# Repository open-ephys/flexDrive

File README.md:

flexDrive
==========

__This design is deprecated, we recommend switching to the newer Open Ephys shuttle drive__ (preprint: https://www.biorxiv.org/content/10.1101/746651v1), (git repository: https://github.com/open-ephys/shuttle-drive). This new design is superior to the flexDrive in all aspects (robustness, travel distance, build speed), and we strongly recommend switching.

The flexDrive is a compact hyperdrive for up to 16 independently movable electrodes. It uses a novel spring mechanism to adjust electrode depth.

This repository only contains design files. See https://open-ephys.atlassian.net/wiki/display/OEW/flexDrive for documentation and assembly instructions.

File types
------------
- .brd = EAGLE board files; describe the physical layout of the printed circuit board
- .md = Markdown files; most likely a README file; can be viewed with any text edtior
- .txt  = standard text files
- "gerber" files (.top, .bsk, .oln, etc.) = contain machine-readable instructions for creating the printed circuit board; these are sent to a fab house (such as Sunstone Circuits) for PCB production
- .SLDPRT files = SolidWorks part files; contain CAD models of 3D components
- .SLDDRW files = SolidWorks drawing files; contain 2D images of components
- .DXF = another type of 2D drawing file that can be opened in Adobe Illustrator or similar software
- .STL files = stereolithography files; can be sent to a rapid prototyping service (such as Shapeways) to create 3D objects
- .pdf files = standard document format for viewing and editing 2D images

Paper
----------

Voigts J, Siegle JH, Pritchett DL and Moore CI (2013). 
The flexDrive: An ultra-light implant for optical control and highly parallel chronic recording of neuronal ensembles in freely moving mice. 
Front. Syst. Neurosci. 7:8. doi: 10.3389/fnsys.2013.00008

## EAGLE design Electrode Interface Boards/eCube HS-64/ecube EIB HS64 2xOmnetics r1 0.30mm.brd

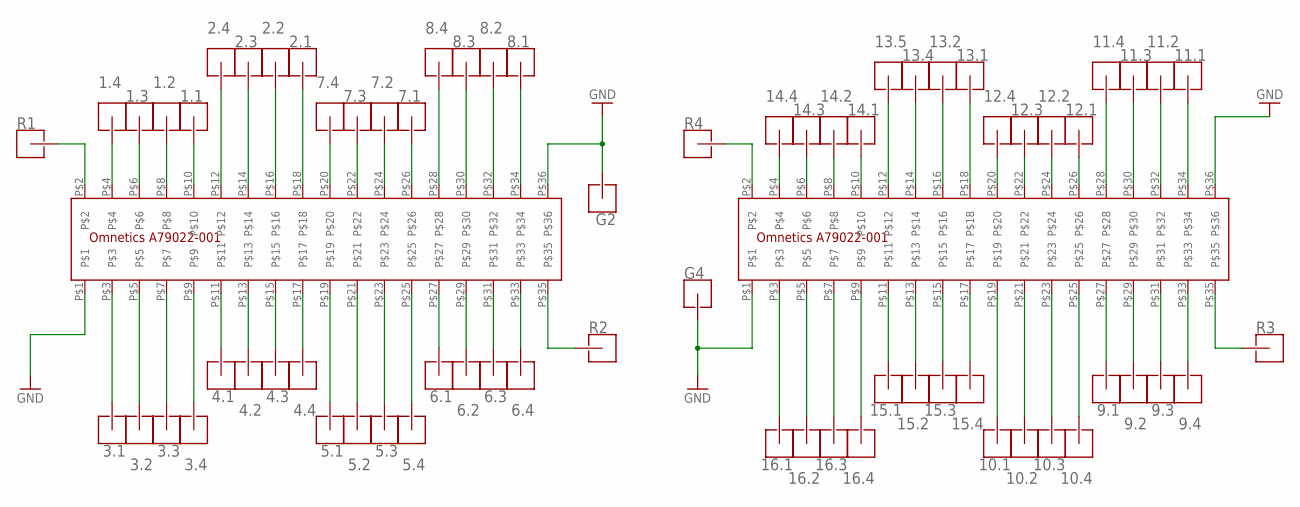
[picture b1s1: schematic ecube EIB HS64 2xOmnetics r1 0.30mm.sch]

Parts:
1.1, 1.2, 1.3, 1.4, 2.1, 2.2, 2.3, 2.4, 3.1, 3.2, 3.3, 3.4, 4.1, 4.2, 4.3, 4.4, 5.1, 5.2, 5.3, 5.4, 6.1, 6.2, 6.3, 6.4, 7.1, 7.2, 7.3, 7.4, 8.1, 8.2, 8.3, 8.4, 9.1, 9.2, 9.3, 9.4, 10.1, 10.2, 10.3, 10.4, 11.1, 11.2, 11.3, 11.4, 12.1, 12.2, 12.3, 12.4, 13.1, 13.2, 13.4, 13.5, 14.1, 14.2, 14.3, 14.4, 15.1, 15.2, 15.3, 15.4, 16.1, 16.2, 16.3, 16.4: HOLE_S_G_PIN_V3; SMALL_GOLD_PIN_V3
G2, G4: HOLE_L_G_PIN_V1; LARGE_GOLD_PIN_V1
R1, R2, R3, R4: HOLE_L_G_PIN_V1; LARGE_GOLD_PIN_V1
U$1, U$2: A79022-001

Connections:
GND: G2.P$1, G4.P$1, U$1.P$1, U$1.P$36, U$2.P$1, U$2.P$36
unnamed: R4.P$1, U$2.P$2
unnamed: R2.P$1, U$1.P$35
unnamed: R1.P$1, U$1.P$2
unnamed: 14.4.P$1, U$2.P$4
unnamed: 14.3.P$1, U$2.P$6
unnamed: 14.2.P$1, U$2.P$8
unnamed: 14.1.P$1, U$2.P$10
unnamed: 13.5.P$1, U$2.P$12
unnamed: 13.4.P$1, U$2.P$14
unnamed: 13.2.P$1, U$2.P$16
unnamed: 13.1.P$1, U$2.P$18
unnamed: 12.4.P$1, U$2.P$20
unnamed: 12.3.P$1, U$2.P$22
unnamed: 12.2.P$1, U$2.P$24
unnamed: 12.1.P$1, U$2.P$26
unnamed: 11.4.P$1, U$2.P$28
unnamed: 11.3.P$1, U$2.P$30
unnamed: 11.2.P$1, U$2.P$32
unnamed: 11.1.P$1, U$2.P$34
unnamed: 9.4.P$1, U$2.P$33
unnamed: 9.3.P$1, U$2.P$31
unnamed: R3.P$1, U$2.P$35
unnamed: 9.2.P$1, U$2.P$29
unnamed: 9.1.P$1, U$2.P$27
unnamed: 10.4.P$1, U$2.P$25
unnamed: 10.3.P$1, U$2.P$23
unnamed: 10.2.P$1, U$2.P$21
unnamed: 10.1.P$1, U$2.P$19
unnamed: 15.4.P$1, U$2.P$17
unnamed: 15.3.P$1, U$2.P$15
unnamed: 15.2.P$1, U$2.P$13
unnamed: 15.1.P$1, U$2.P$11
unnamed: 3.1.P$1, U$1.P$3
unnamed: 16.4.P$1, U$2.P$9
unnamed: 16.3.P$1, U$2.P$7
unnamed: 3.2.P$1, U$1.P$5
unnamed: 3.3.P$1, U$1.P$7
unnamed: 3.4.P$1, U$1.P$9
unnamed: 4.1.P$1, U$1.P$11
unnamed: 4.2.P$1, U$1.P$13
unnamed: 4.3.P$1, U$1.P$15
unnamed: 4.4.P$1, U$1.P$17
unnamed: 5.1.P$1, U$1.P$19
unnamed: 5.2.P$1, U$1.P$21
unnamed: 5.3.P$1, U$1.P$23
unnamed: 5.4.P$1, U$1.P$25
unnamed: 6.1.P$1, U$1.P$27
unnamed: 6.2.P$1, U$1.P$29
unnamed: 6.3.P$1, U$1.P$31
unnamed: 6.4.P$1, U$1.P$33
unnamed: 16.2.P$1, U$2.P$5
unnamed: 16.1.P$1, U$2.P$3
unnamed: 8.1.P$1, U$1.P$34
unnamed: 8.2.P$1, U$1.P$32
unnamed: 8.3.P$1, U$1.P$30
unnamed: 8.4.P$1, U$1.P$28
unnamed: 7.1.P$1, U$1.P$26
unnamed: 7.2.P$1, U$1.P$24
unnamed: 7.3.P$1, U$1.P$22
unnamed: 7.4.P$1, U$1.P$20
unnamed: 2.1.P$1, U$1.P$18
unnamed: 2.2.P$1, U$1.P$16
unnamed: 2.3.P$1, U$1.P$14
unnamed: 2.4.P$1, U$1.P$12
unnamed: 1.1.P$1, U$1.P$10
unnamed: 1.2.P$1, U$1.P$8
unnamed: 1.3.P$1, U$1.P$6
unnamed: 1.4.P$1, U$1.P$4

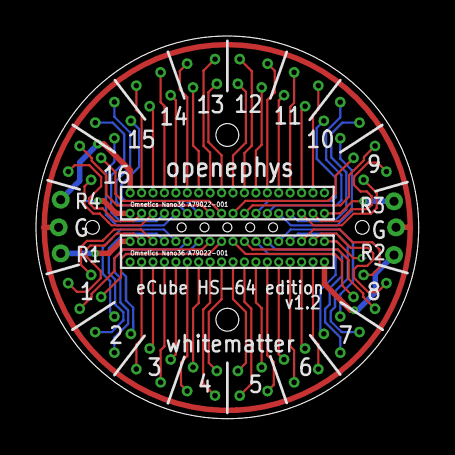
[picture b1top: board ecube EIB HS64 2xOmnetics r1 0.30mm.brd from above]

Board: 2 copper layers, 21.3 x 21.3 mm, 72 parts (0 on the bottom side), 69 nets.

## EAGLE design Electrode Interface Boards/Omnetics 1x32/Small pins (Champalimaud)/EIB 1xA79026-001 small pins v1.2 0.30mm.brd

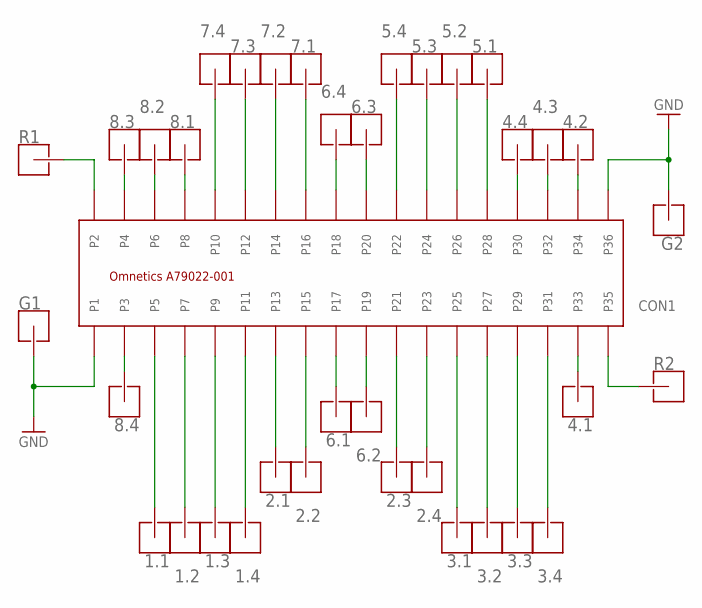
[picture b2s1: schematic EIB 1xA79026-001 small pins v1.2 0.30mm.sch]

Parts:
1.1, 1.2, 1.3, 1.4, 2.1, 2.2, 2.3, 2.4, 3.1, 3.2, 3.3, 3.4, 4.1, 4.2, 4.3, 4.4, 5.1, 5.2, 5.3, 5.4, 6.1, 6.2, 6.3, 6.4, 7.1, 7.2, 7.3, 7.4, 8.1, 8.2, 8.3, 8.4: HOLE_S_G_PIN_V3; SMALL_GOLD_PIN_V3
CON1: A79022-001_MALESMD; A79026-001_MALE
G1, G2: HOLE_S_G_PIN_V3; SMALL_GOLD_PIN_V3
R1, R2: HOLE_S_G_PIN_V3; SMALL_GOLD_PIN_V3

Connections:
GND: CON1.P1, CON1.P36, G1.P$1, G2.P$1
unnamed: 1.1.P$1, CON1.P5
unnamed: 1.2.P$1, CON1.P7
unnamed: 1.3.P$1, CON1.P9
unnamed: 4.1.P$1, CON1.P33
unnamed: 4.3.P$1, CON1.P32
unnamed: 4.2.P$1, CON1.P34
unnamed: 1.4.P$1, CON1.P11
unnamed: 4.4.P$1, CON1.P30
unnamed: 6.1.P$1, CON1.P17
unnamed: 6.2.P$1, CON1.P19
unnamed: 6.3.P$1, CON1.P20
unnamed: 7.3.P$1, CON1.P12
unnamed: 2.1.P$1, CON1.P13
unnamed: 2.2.P$1, CON1.P15
unnamed: 2.3.P$1, CON1.P21
unnamed: 2.4.P$1, CON1.P23
unnamed: 3.1.P$1, CON1.P25
unnamed: 3.2.P$1, CON1.P27
unnamed: 3.3.P$1, CON1.P29
unnamed: 3.4.P$1, CON1.P31
unnamed: 6.4.P$1, CON1.P18
unnamed: 8.4.P$1, CON1.P3
unnamed: 8.3.P$1, CON1.P4
unnamed: 8.2.P$1, CON1.P6
unnamed: 8.1.P$1, CON1.P8
unnamed: 7.2.P$1, CON1.P14
unnamed: 7.1.P$1, CON1.P16
unnamed: 7.4.P$1, CON1.P10
unnamed: 5.1.P$1, CON1.P28
unnamed: 5.2.P$1, CON1.P26
unnamed: 5.4.P$1, CON1.P22
unnamed: 5.3.P$1, CON1.P24
unnamed: CON1.P2, R1.P$1
unnamed: CON1.P35, R2.P$1

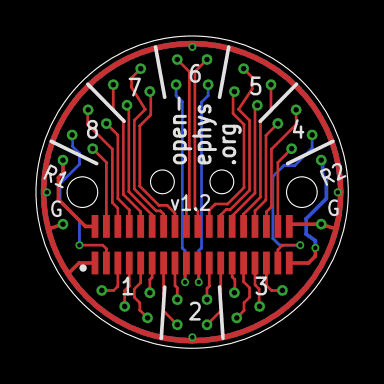
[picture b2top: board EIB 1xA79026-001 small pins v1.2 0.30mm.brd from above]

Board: 2 copper layers, 17.3 x 17.3 mm, 37 parts (0 on the bottom side), 35 nets.

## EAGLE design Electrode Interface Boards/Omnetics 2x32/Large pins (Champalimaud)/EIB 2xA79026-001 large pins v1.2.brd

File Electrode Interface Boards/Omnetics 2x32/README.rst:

2x Omnetics 36-channel "nano-strip" connectors, 4 guide posts
---------------------------------------------------------------------------------

The 64ch_eib_omnetics_3fibers Electrode Interface Board  (EIB) is designed to form a connection between 64 microwire electrodes or individual wires forming stereotrodes or tetrodes, and two 32 channel omnetics connectors.

The 'offset variant' provides more space between the two omnetics connectors and can be soldered by hand if needed, but won't fit the 64 channel headstage.

The aligned variant fits the 64 channel headstage, and can also be used with 2x 32 channel headstages, if they're aligned with the PCB facing away from the center (this will affect the channel mapping).

See the documentation on https://open-ephys.atlassian.net/wiki/display/OEW/flexDrive for building and use instructions.

**WARNING:** These designs will not work if fabricated as 'standard quality' PCB, see Fabrication instructions and get in touch with your PCB maker before placing orders!

Connectors on EIB:
~~~~~~~~~~~~~~~

* male surface-mount vertical (A79026-001 / NPD-36-VV-GS)

Connectors on Headstage:
~~~~~~~~~~~~~~~~~~
 
* female surface-mount horizontal (A79025-001 / NSD-36-AA-GS)
* female surface-mount vertical (A79027-001 / NSD-36-VV-GS)

Pin mapping:
~~~~~~~~~~~~~~~~~~
The pin mapping for the GROUND and REFERENCE channels on the offset connector EIB are compatible with the mapping on the Intan evaluation system headstages (http://www.intantech.com/files/Intan_RHD2000_eval_system.pdf) and the open-ephys headstages (open-ephys.org)

(viewed down onto the eib, looking onto the bottom of the headstage connector this would be flipped)

| ref  | ch | ch | ... | ch | gnd |
| gnd | ch | ch | ... | ch | ref |

For channel mappings of individual EIB designs, look at the documenttaiopn in that EIBs folder. Orientation of headstages affects the channel mapping - when in doubt you should sanity check your mapping by connecting a EIB to your system and grounding out or injecting a signal on individual vias.

Hole sizes:
~~~~~~~~~~~~~~~~~~

The hole size on this EIB (0.3mm) is suited for use with SMALL neuralynx gold pins (http://neuralynx.com/products/electrode_interface_boards/eib_pins) 

The three mounting holes for optical fiber ferrules are sized for use with 1.25mm OD ferrules.

See the documentation on https://open-ephys.atlassian.net/wiki/display/OEW/flexDrive for building and use instructions.

Fabrication instructions:
~~~~~~~~~~~~~~~~~~

These EIBs can be fabricated with the following process
- 5mil trace with / 5mil trace space
- gold immersion finish
- 0.03 inch board thickness (not critical, can be made thicker)
- top silkscreen

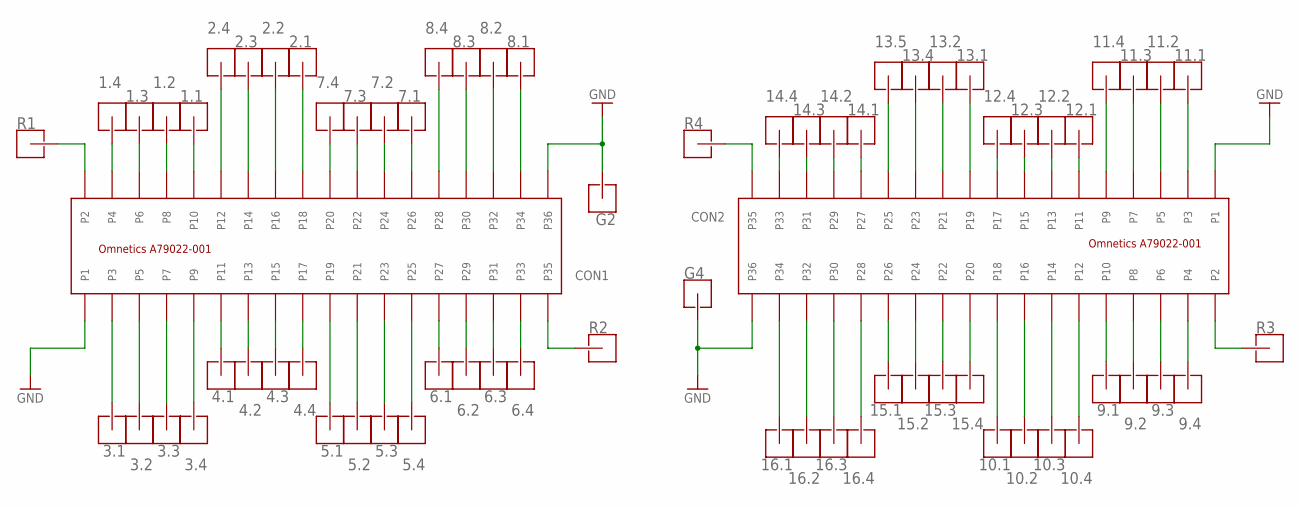
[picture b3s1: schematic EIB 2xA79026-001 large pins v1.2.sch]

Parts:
1.1, 1.2, 1.3, 1.4, 2.1, 2.2, 2.3, 2.4, 3.1, 3.2, 3.3, 3.4, 4.1, 4.2, 4.3, 4.4, 5.1, 5.2, 5.3, 5.4, 6.1, 6.2, 6.3, 6.4, 7.1, 7.2, 7.3, 7.4, 8.1, 8.2, 8.3, 8.4, 9.1, 9.2, 9.3, 9.4, 10.1, 10.2, 10.3, 10.4, 11.1, 11.2, 11.3, 11.4, 12.1, 12.2, 12.3, 12.4, 13.1, 13.2, 13.4, 13.5, 14.1, 14.2, 14.3, 14.4, 15.1, 15.2, 15.3, 15.4, 16.1, 16.2, 16.3, 16.4: HOLE_L_G_PIN_V5; LARGE_GOLD_PIN_V5
CON1, CON2: A79022-001_MALESMD; A79026-001_MALE
G2, G4: HOLE_L_G_PIN_V5; LARGE_GOLD_PIN_V5
R1, R2, R3, R4: HOLE_L_G_PIN_V5; LARGE_GOLD_PIN_V5

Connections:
GND: CON1.P1, CON1.P36, CON2.P1, CON2.P36, G2.P$1, G4.P$1
unnamed: 11.2.P$1, CON2.P5
unnamed: 11.3.P$1, CON2.P7
unnamed: 11.4.P$1, CON2.P9
unnamed: 14.4.P$1, CON2.P33
unnamed: 16.2.P$1, CON2.P32
unnamed: 16.1.P$1, CON2.P34
unnamed: 12.1.P$1, CON2.P11
unnamed: 16.3.P$1, CON2.P30
unnamed: 12.4.P$1, CON2.P17
unnamed: 13.1.P$1, CON2.P19
unnamed: 15.4.P$1, CON2.P20
unnamed: 10.4.P$1, CON2.P12
unnamed: 12.2.P$1, CON2.P13
unnamed: 12.3.P$1, CON2.P15
unnamed: 13.2.P$1, CON2.P21
unnamed: 13.4.P$1, CON2.P23
unnamed: 13.5.P$1, CON2.P25
unnamed: 14.1.P$1, CON2.P27
unnamed: 14.2.P$1, CON2.P29
unnamed: 14.3.P$1, CON2.P31
unnamed: 10.1.P$1, CON2.P18
unnamed: 11.1.P$1, CON2.P3
unnamed: 9.4.P$1, CON2.P4
unnamed: 9.3.P$1, CON2.P6
unnamed: 9.2.P$1, CON2.P8
unnamed: 10.3.P$1, CON2.P14
unnamed: 10.2.P$1, CON2.P16
unnamed: 9.1.P$1, CON2.P10
unnamed: 16.4.P$1, CON2.P28
unnamed: 15.1.P$1, CON2.P26
unnamed: 15.3.P$1, CON2.P22
unnamed: 15.2.P$1, CON2.P24
unnamed: CON1.P2, R1.P$1
unnamed: CON2.P2, R3.P$1
unnamed: CON2.P35, R4.P$1
unnamed: CON1.P35, R2.P$1
unnamed: 3.2.P$1, CON1.P5
unnamed: 3.3.P$1, CON1.P7
unnamed: 3.4.P$1, CON1.P9
unnamed: 4.1.P$1, CON1.P11
unnamed: 4.2.P$1, CON1.P13
unnamed: 4.3.P$1, CON1.P15
unnamed: 5.2.P$1, CON1.P21
unnamed: 5.3.P$1, CON1.P23
unnamed: 5.4.P$1, CON1.P25
unnamed: 7.4.P$1, CON1.P20
unnamed: 7.3.P$1, CON1.P22
unnamed: 7.2.P$1, CON1.P24
unnamed: 4.4.P$1, CON1.P17
unnamed: 5.1.P$1, CON1.P19
unnamed: 7.1.P$1, CON1.P26
unnamed: 2.1.P$1, CON1.P18
unnamed: 3.1.P$1, CON1.P3
unnamed: 1.4.P$1, CON1.P4
unnamed: 1.3.P$1, CON1.P6
unnamed: 1.2.P$1, CON1.P8
unnamed: 2.4.P$1, CON1.P12
unnamed: 2.3.P$1, CON1.P14
unnamed: 2.2.P$1, CON1.P16
unnamed: 1.1.P$1, CON1.P10
unnamed: 6.4.P$1, CON1.P33
unnamed: 6.1.P$1, CON1.P27
unnamed: 6.2.P$1, CON1.P29
unnamed: 6.3.P$1, CON1.P31
unnamed: 8.1.P$1, CON1.P34
unnamed: 8.2.P$1, CON1.P32
unnamed: 8.3.P$1, CON1.P30
unnamed: 8.4.P$1, CON1.P28

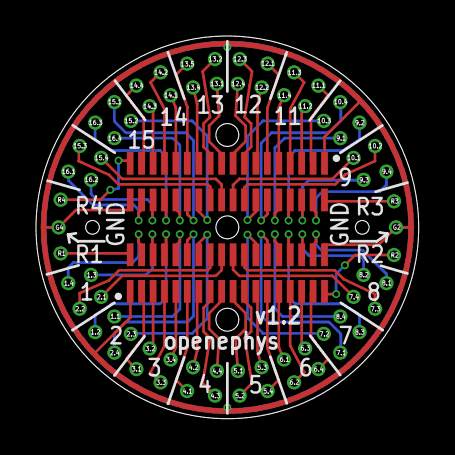
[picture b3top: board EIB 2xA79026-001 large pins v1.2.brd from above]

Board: 2 copper layers, 21.3 x 21.3 mm, 72 parts (0 on the bottom side), 69 nets.

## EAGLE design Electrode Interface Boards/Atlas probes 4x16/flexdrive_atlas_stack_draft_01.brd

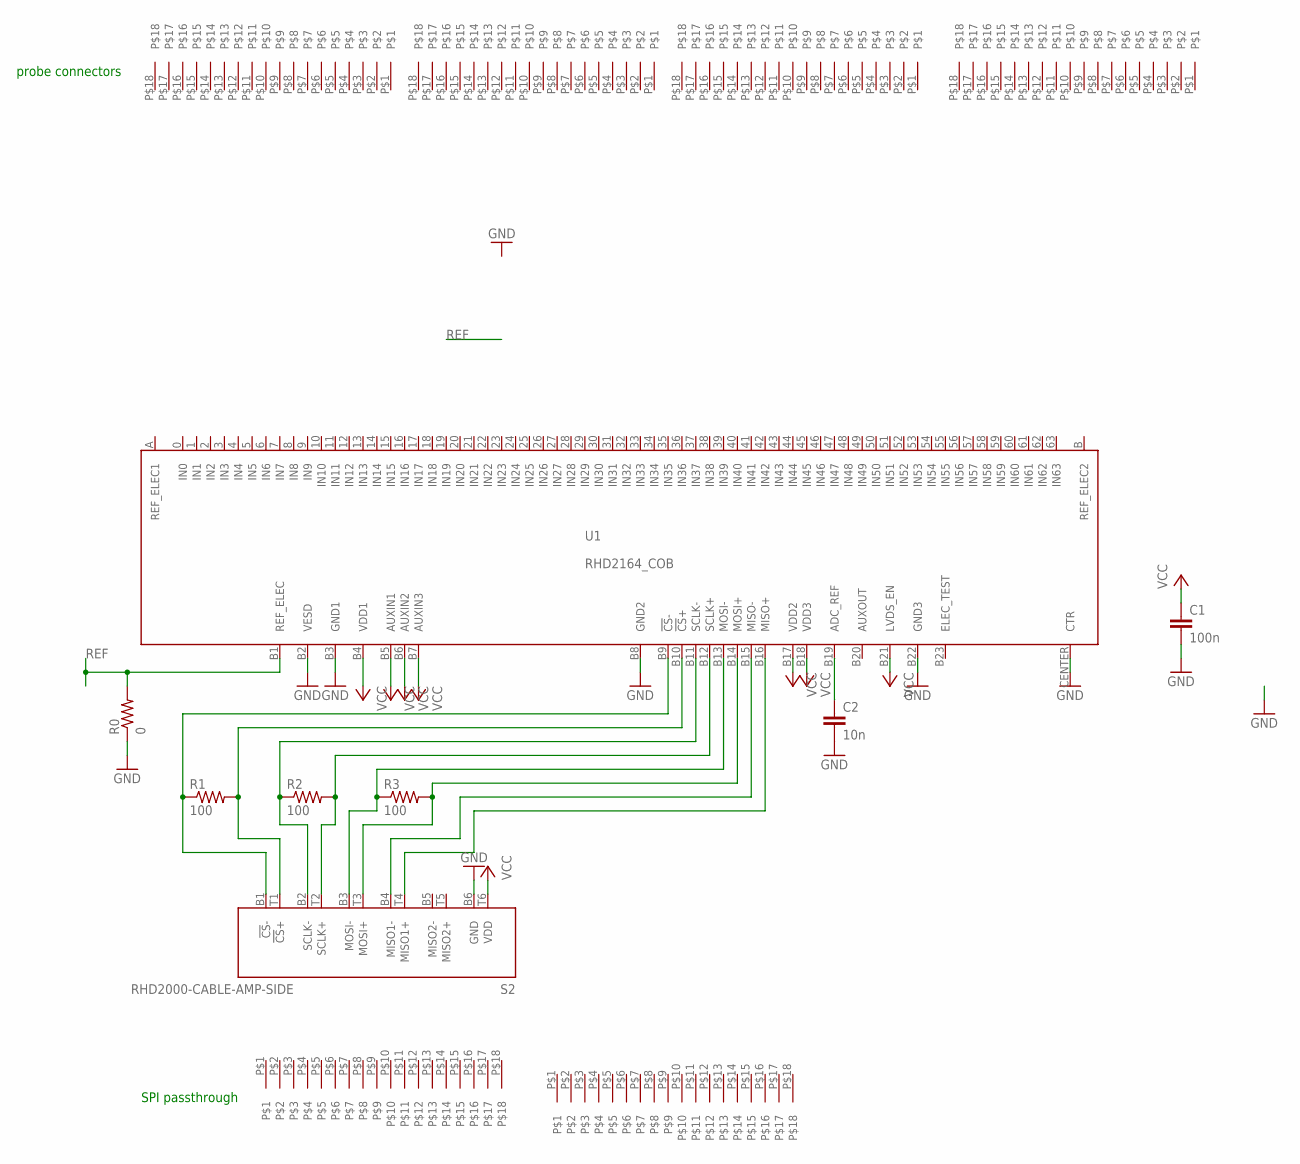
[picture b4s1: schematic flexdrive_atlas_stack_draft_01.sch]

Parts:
C1: 100n; 0402
C2: 10n; 0201
R0: 0; 0402
R1, R2, R3: 100; 0201
S2: RHD2000-CABLE-AMP-SIDE; OMNETICS_PZN-12-AA
U1: RHD2164_COB
U$1, U$2, U$3, U$4, U$5, U$6: 18PIN_035MM_SLIMSTACK; 18PIN_025MM_SLIMSTACK

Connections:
GND: C1.2, C2.2, R0.1, S2.B6 (GND), U1.B2 (VESD), U1.B3 (GND1), U1.B8 (GND2), U1.B22 (GND3), U1.CENTER (CTR)
unnamed: S2.T4 (MISO1+), U1.B16 (MISO+)
unnamed: R1.1, S2.B1 (!CS!-), U1.B9 (!CS!-)
unnamed: R1.2, S2.T1 (!CS!+), U1.B10 (!CS!+)
unnamed: R2.1, S2.B2 (SCLK-), U1.B11 (SCLK-)
unnamed: R2.2, S2.T2 (SCLK+), U1.B12 (SCLK+)
unnamed: R3.1, S2.B3 (MOSI-), U1.B13 (MOSI-)
unnamed: R3.2, S2.T3 (MOSI+), U1.B14 (MOSI+)
unnamed: S2.B4 (MISO1-), U1.B15 (MISO-)
unnamed: C2.1, U1.B19 (ADC_REF)
REF: R0.2, U1.B1 (REF_ELEC)
VCC: C1.1, S2.T6 (VDD), U1.B4 (VDD1), U1.B5 (AUXIN1), U1.B6 (AUXIN2), U1.B7 (AUXIN3), U1.B17 (VDD2), U1.B18 (VDD3), U1.B21 (LVDS_EN)

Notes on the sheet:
SPI passthrough
probe connectors

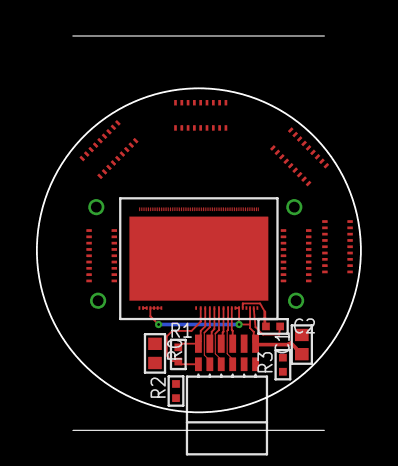
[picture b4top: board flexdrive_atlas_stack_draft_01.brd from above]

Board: 2 copper layers, 18.0 x 18.0 mm, 14 parts (0 on the bottom side), 12 nets.

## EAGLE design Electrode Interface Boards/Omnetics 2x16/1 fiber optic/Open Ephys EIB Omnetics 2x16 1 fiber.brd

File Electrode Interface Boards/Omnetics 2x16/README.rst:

Omnetics 18-channel "nano-strip" connectors, 4 guide posts
---------------------------------------------------------------------------------

The 32ch_eib_omnetics_2fibers and 32ch_eib_omnetics_1fiber Electrode Interface Boards (EIB) aredesigned to form a connection between 32microwire electrodes or individual wires forming stereotrodes or tetrodes, and two 16 channel omnetics connectors.

See the documentation on http://github.com/open-ephys/flexDrive for building and use instructions.

Connectors on EIB:
~~~~~~~~~~~~~~~

* male surface-mount vertical (A79042-001 / NPD-18-VV-GS)

Connectors on Headstage:
~~~~~~~~~~~~~~~~~~
 
* female surface mount horizontal (A79041-001 / NSD-18-AA-GS)
* female surface mount vertical (A79043-001 / NSD-18-VV-GS)

Pin mapping:
~~~~~~~~~~~~~~~~~~
The pin mapping for the GROUND and REFERENCE channels on this EIB are compatible with the mapping on the standard omnetics 16 channel headstages.

Hole sizes:
~~~~~~~~~~~~~~~~~~
The hole size on this EIB (0.5mm) is suited for use with LARGE neuralynx gold pins (http://neuralynx.com/products/electrode_interface_boards/eib_pins) 

The mounting holes for optical fiber ferrules are sized for use with 1.25mm OD ferrules.

Fabrication instructions:
~~~~~~~~~~~~~~~~~~

This EIB can be fabricated with the following process
- 8mil trace with / 8mil trace space
- 0.03 inch board thickness (not critical, can be made thicker)
- top silkscreen

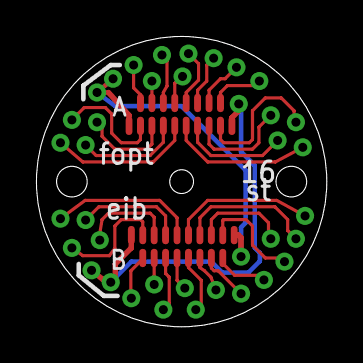
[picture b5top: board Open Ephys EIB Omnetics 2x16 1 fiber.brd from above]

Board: 2 copper layers, 16.1 x 16.1 mm, 40 parts (0 on the bottom side), 34 nets.

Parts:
U$1, U$2: OMNETICS_FE18
U$3, U$4, U$5, U$6, U$7, U$8, U$9, U$10, U$11, U$12, U$13, U$14, U$15, U$16, U$17, U$18, U$19, U$20, U$21, U$22, U$23, U$24, U$25, U$26, U$27, U$28, U$29, U$30, U$31, U$32, U$33, U$34, U$35, U$36, U$37, U$38, U$39, U$40: GOLDPINLARGE; LARGEGOLDPIN

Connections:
unnamed: U$2.P$15, U$28.P1
unnamed: U$2.P$14, U$29.P1
unnamed: U$1.P$8, U$3.P1
unnamed: U$1.P$7, U$5.P1
unnamed: U$1.P$6, U$4.P1
unnamed: U$1.P$5, U$6.P1
unnamed: U$1.P$4, U$7.P1
unnamed: U$1.P$3, U$8.P1
unnamed: U$1.P$2, U$9.P1
unnamed: U$1.P$1, U$10.P1
unnamed: U$1.P$16, U$18.P1
unnamed: U$1.P$15, U$17.P1
unnamed: U$1.P$14, U$16.P1
unnamed: U$1.P$13, U$15.P1
unnamed: U$1.P$12, U$14.P1
unnamed: U$1.P$11, U$13.P1
unnamed: U$1.P$10, U$12.P1
unnamed: U$1.P$9, U$11.P1
unnamed: U$2.P$1, U$26.P1
unnamed: U$2.P$2, U$25.P1
unnamed: U$2.P$3, U$24.P1
unnamed: U$2.P$4, U$23.P1
unnamed: U$2.P$5, U$22.P1
unnamed: U$2.P$6, U$21.P1
unnamed: U$2.P$7, U$20.P1
unnamed: U$2.P$8, U$19.P1
unnamed: U$2.P$9, U$36.P1
unnamed: U$2.P$10, U$35.P1
unnamed: U$2.P$11, U$34.P1
unnamed: U$2.P$12, U$33.P1
unnamed: U$2.P$13, U$32.P1
unnamed: U$2.P$16, U$27.P1
unnamed: U$1.P$17, U$2.P$17, U$31.P1, U$39.P1, U$40.P1
REF1: U$1.P$18, U$2.P$18, U$30.P1, U$37.P1, U$38.P1

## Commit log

2012-08-31 Added license files
2013-03-14 initial commit 64 channel flexdrive EIB
    added brd file and gerber files for first production run
2013-03-14 initial commit 32 channel flexdrive EIBs
    added brd files for two variants of the 32ch eib, for one and two fibers
2013-03-25 Create gh-pages branch via GitHub
2013-03-25 updated readme with link to github page
2013-03-25 testing checkout
2013-03-25 test includes
2013-03-25 jekyll config update
2013-03-25 test
2013-03-25 initial commit flexDrive website
2013-03-25 fixed links and includes
2013-03-25 fixed naming typo
2013-03-25 testing headers
2013-03-25 updated jekyll headers
2013-03-25 fixed includes
2013-03-25 updated src file links
2013-03-25 updated headers
2013-03-25 updated title
2013-03-25 updated subtitle
2013-03-26 initial commit shield and cap templates
2013-03-26 initial commit drive spring files
2013-03-26 initial commit flexDrive body source files
2013-03-26 added drive body drawing pdf
2013-03-26 added bilateral hippocampus implant body
2013-03-26 moved URL in title line
2013-03-26 commented out manuscript link
    manuscript goes online when the paper is in preprint
2013-03-26 fixed drc errors
    changed mounting holes to 0.762mm
    moved some electrode pin vias away from edge
    re-routed central traces around ferrule hole
2013-03-27 added note on TI screws
2013-03-27 fixed links
2013-03-28 Update README and add .gitignore file
2013-03-30 added frontiers link
2013-03-30 updated citation
2013-04-02 fixed 5mil spacing drc error
    changed some vias to 0.008" to make more space for the routing between
    the omnetics connectors
2013-04-03 added 32ch eib variant with 3 ferrule holes
    requires 5mil traces
2013-04-12 added solidworks file for spring without kerf
    kerf is not accounted for in this part
    There are areas where a 13mil kerf will not be able to follow the
    outlines, such as the cutout where the screw will fit - it is probably
    ok to just not cut as deep of a cutout there.
2013-04-14 Remove 32ch + 64ch EIB folders
2013-04-14 Add new EIB directories
2013-04-14 Rename README files
2013-04-15 Add Gerber files for 1x32 EIB
2013-04-15 Add Gerber files and images for EIBs
2013-04-22 Fix spacing issues on 2x16 boards
2013-04-23 Update Gerber files
2013-04-23 Fix unconnected trace on 1x32 EIB
2013-05-02 add CA1 bilateral STL
2013-05-02 added dxf file for spring with no kerf adjustment
2013-05-02 added printout sheet for 64ch EIB
2013-05-07 Update design for bilateral drive
2013-05-11 fixed link
2013-05-21 moved mounting holes to fix spacing violation
2013-05-21 updated gerber files
2013-05-25 IGS and STEP files for bilateral CA1 drive
    committing new files in josh's design
2013-05-28 Fixed spacing issue
2013-08-07 Made kerf adjusted new rev
    smaller heads no hooks, for 13mil kerf
    should be functionally similar to the not kerf adjusted version
2013-08-15 Add drive data sheet for 1x32 Omnetics EIB
2013-11-05 Add Gerber files for 1x32 design
2013-11-07 Add Eagle and AI files for 2x32 large gold pin version
2013-12-03 Reorganized 2x32eib to large and small pin folders
2014-02-06 Add drive base for 64-channel large EIBs
2014-02-11 organized into folders for small/large EIBs
2014-02-12 added PCB spec warning and updated links
2014-03-03 changed readme link to point to wiki
2014-06-22 Initial commit This is a _very_ rough draft to test the fit of 4 16ch connectors for laminar probe flex cables. There's also 2 connectors for stacking 2 of these EIBs with MISO passthrough. The pass-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
2014-08-09 Update Sunstone gerber files
2014-10-01 Reorganized folders for 64ch headstages
2014-10-01 Updated 64ch headstage readme
2014-10-01 Added 64ch readme
2014-10-02 Updated spring design
    no big changes, mostly cleared up names and added some length to fork
    tips
2014-10-03 Added gerber files
2014-10-03 Added documentation
2014-10-22 Small revisions to spring
    Heads came out a bit short on 13mil kerf EDM, made them a tad longer.
2014-11-18 Added Orcad source file for 2x32 ch EIB from Bernhard Englitz
2014-12-16 re-created Omnetics 1x32 gerbers
    were missing drill files
2015-06-21 Add Champalimaud EIB designs
2016-02-22 Add EIB designs for eCube headstage
2016-04-16 Added Gerber files for Champalimaud designs
2016-08-29 added spring design with no baked-in kerf adjustments
2016-08-29 added spring in DXF,IGS and STEP formats
2017-07-13 added spring in more formats
2019-08-25 added note about switching to new design
